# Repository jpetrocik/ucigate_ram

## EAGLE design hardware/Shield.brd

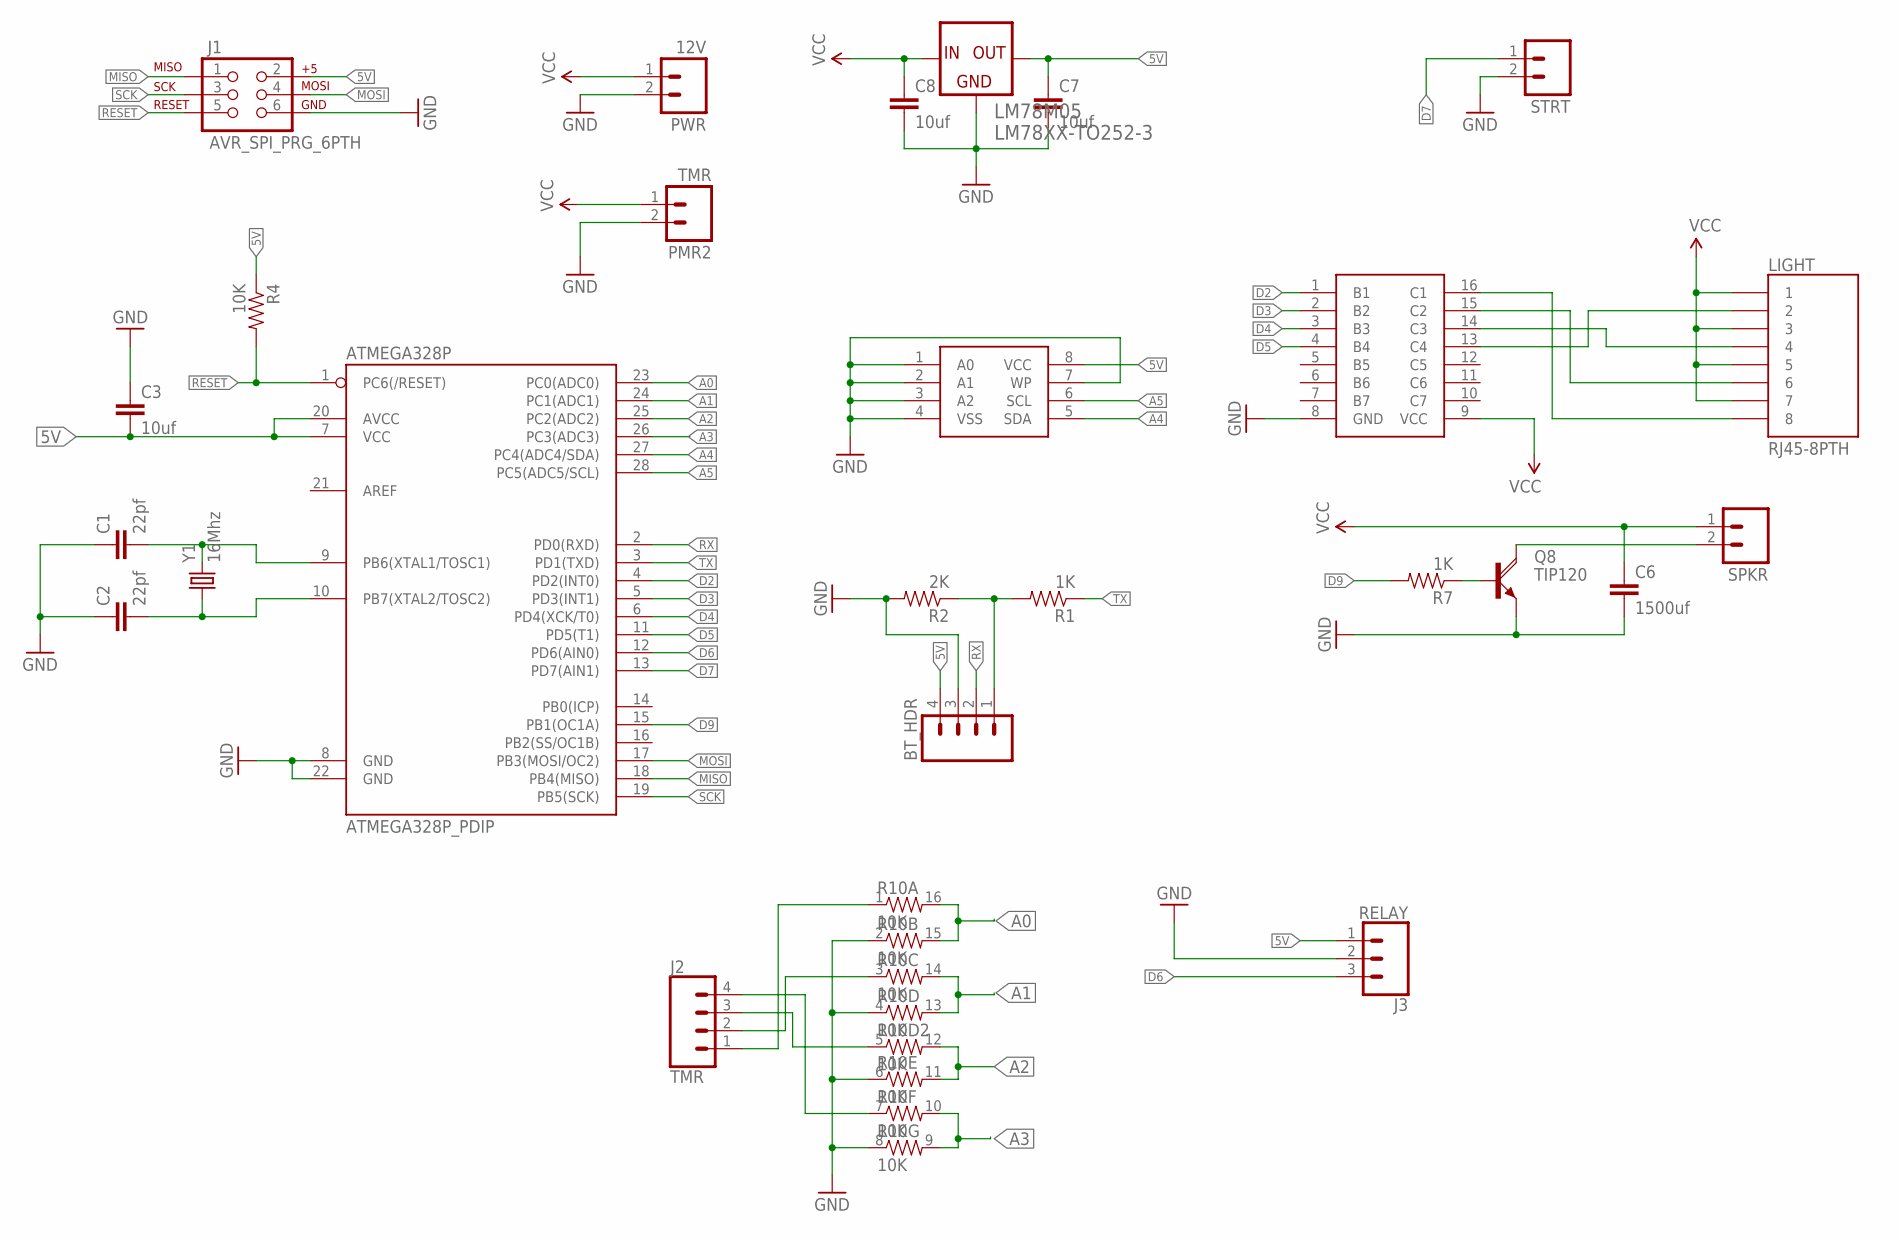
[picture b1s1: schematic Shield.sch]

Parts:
24AA512: 24AAXXX; SOIC-8-EIAJ
ATMEGA328P: ATMEGA328P_PDIP; DIL28-3
BT_HDR: M04PTH; 1X04@1
C1, C2: 22pf; 1206
C3: 10uf; 1206
C6: 1500uf; CAP-PTH-5MM
C7, C8: 10uf; CAP-PTH-SMALL
J1: AVR_SPI_PRG_6PTH; 2X3
J2: TMR; SCREWTERMINAL-3.5MM-4
J3: RELAY; SCREWTERMINAL-3.5MM-3
LIGHT: RJ45-8PTH; RJ45-8
LM78M05: LM78XX-TO252-3; TO252-3
MC1413D: MC1413D; SO016
PMR2: TMR; SCREWTERMINAL-3.5MM-2
PWR: 12V; SCREWTERMINAL-3.5MM-2
Q8: TIP120; TO220V
R1, R7: 1K; 1206
R2: 2K; 1206
R4: 10K; 1206
R10: 10K; SO016
SPKR: M023.5MM; SCREWTERMINAL-3.5MM-2
STRT: M023.5MM; SCREWTERMINAL-3.5MM-2
Y1: 16Mhz; HC49US

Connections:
5V: 24AA512.8 (VCC), ATMEGA328P.7 (VCC), ATMEGA328P.20 (AVCC), BT_HDR.4, C3.2, C7.1, J1.2, J3.1, LM78M05.3 (OUT), R4.1
A0: ATMEGA328P.23 (PC0(ADC0)), R10.15 (2), R10.16 (2)
A1: ATMEGA328P.24 (PC1(ADC1)), R10.13 (2), R10.14 (2)
A2: ATMEGA328P.25 (PC2(ADC2)), R10.11 (2), R10.12 (2)
A3: ATMEGA328P.26 (PC3(ADC3)), R10.9 (2), R10.10 (2)
A4: 24AA512.5 (SDA), ATMEGA328P.27 (PC4(ADC4/SDA))
A5: 24AA512.6 (SCL), ATMEGA328P.28 (PC5(ADC5/SCL))
D2: ATMEGA328P.4 (PD2(INT0)), MC1413D.1 (B1)
D3: ATMEGA328P.5 (PD3(INT1)), MC1413D.2 (B2)
D4: ATMEGA328P.6 (PD4(XCK/T0)), MC1413D.3 (B3)
D5: ATMEGA328P.11 (PD5(T1)), MC1413D.4 (B4)
D6: ATMEGA328P.12 (PD6(AIN0)), J3.3
D7: ATMEGA328P.13 (PD7(AIN1)), STRT.1
D9: ATMEGA328P.15 (PB1(OC1A)), R7.2
GND: 24AA512.1 (A0), 24AA512.2 (A1), 24AA512.3 (A2), 24AA512.4 (VSS), 24AA512.7 (WP), ATMEGA328P.8 (GND), ATMEGA328P.22 (GND), BT_HDR.3, C1.1, C2.1, C3.1, C6.2, C7.2, C8.2, J1.6, J3.2, LM78M05.2 (COM), MC1413D.8 (GND), PMR2.2, PWR.2, Q8.3 (E), R2.2, R10.2 (1), R10.4 (1), R10.6 (1), R10.8 (1), STRT.2
MISO: ATMEGA328P.18 (PB4(MISO)), J1.1
MOSI: ATMEGA328P.17 (PB3(MOSI/OC2)), J1.4
unnamed: BT_HDR.1, R1.2, R2.1
unnamed: LIGHT.8, MC1413D.16 (C1)
unnamed: LIGHT.4, MC1413D.14 (C3)
unnamed: LIGHT.2, MC1413D.13 (C4)
unnamed: LIGHT.6, MC1413D.15 (C2)
unnamed: J2.1, R10.1
unnamed: J2.4, R10.7 (1)
unnamed: Q8.2 (C), SPKR.2
unnamed: ATMEGA328P.9 (PB6(XTAL1/TOSC1)), C1.2, Y1.2
unnamed: J2.2, R10.3 (1)
unnamed: Q8.1 (B), R7.1
unnamed: J2.3, R10.5 (1)
unnamed: ATMEGA328P.10 (PB7(XTAL2/TOSC2)), C2.2, Y1.1
RESET: ATMEGA328P.1 (PC6(/RESET)), J1.5, R4.2
RX: ATMEGA328P.2 (PD0(RXD)), BT_HDR.2
SCK: ATMEGA328P.19 (PB5(SCK)), J1.3
TX: ATMEGA328P.3 (PD1(TXD)), R1.1
VCC: C6.1, C8.1, LIGHT.1, LIGHT.3, LIGHT.5, LIGHT.7, LM78M05.1 (IN), MC1413D.9 (VCC), PMR2.1, PWR.1, SPKR.1

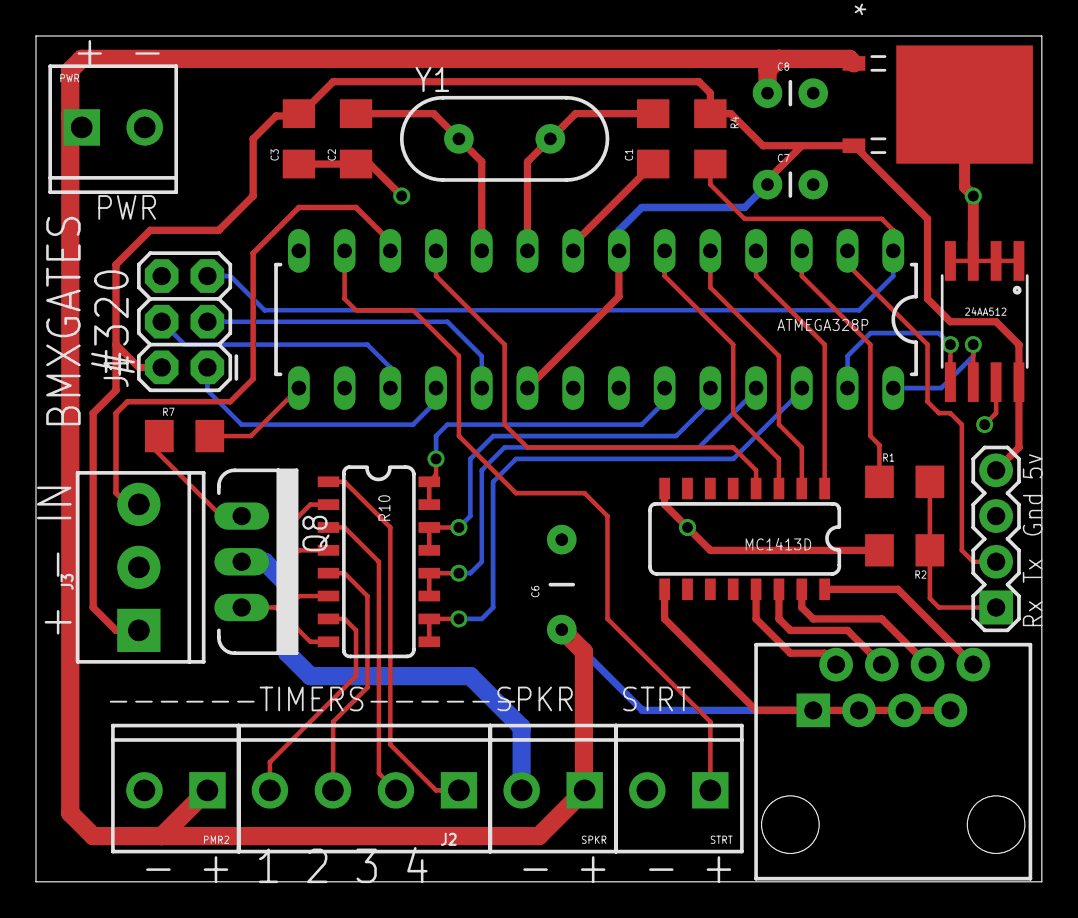
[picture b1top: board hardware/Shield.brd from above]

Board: 2 copper layers, 55.9 x 47.0 mm, 26 parts (0 on the bottom side), 35 nets.

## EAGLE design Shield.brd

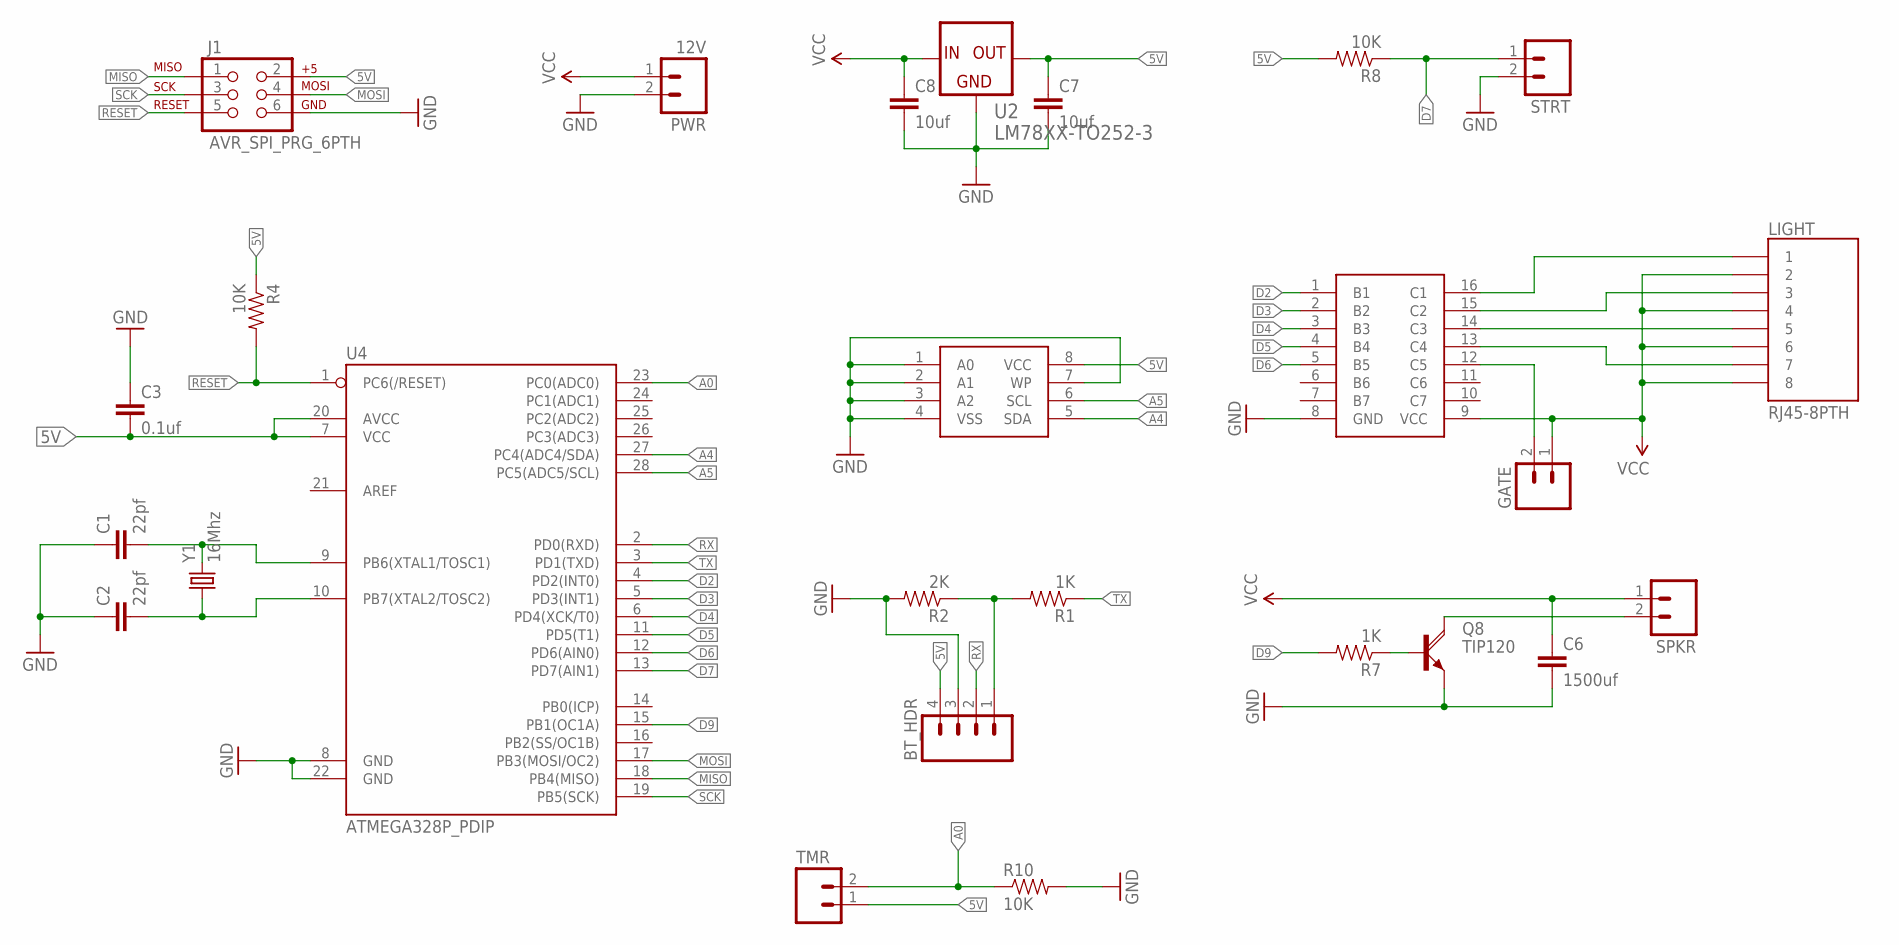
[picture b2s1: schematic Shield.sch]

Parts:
BT_HDR: M04PTH; 1X04
C1, C2: 22pf; 1206
C3: 0.1uf; 1206
C6: 1500uf; CAP-PTH-5MM
C7, C8: 10uf; CAP-PTH-SMALL
GATE: M023.5MM; SCREWTERMINAL-3.5MM-2
J1: AVR_SPI_PRG_6PTH; 2X3
LIGHT: RJ45-8PTH; RJ45-8
PWR: 12V; SCREWTERMINAL-3.5MM-2
Q8: TIP120; TO220V
R1, R7: 1K; 1206
R2: 2K; 1206
R4, R8, R10: 10K; 1206
SPKR: M023.5MM; SCREWTERMINAL-3.5MM-2
STRT: M023.5MM; SCREWTERMINAL-3.5MM-2
TMR: M023.5MM; SCREWTERMINAL-3.5MM-2
U2: LM78XX-TO252-3; TO252-3
U4: ATMEGA328P_PDIP; DIL28-3
U$1: MC1413D; SO016
U$2: 24AAXXX; SOIC-8-EIAJ
Y1: 16Mhz; HC49US

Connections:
5V: BT_HDR.4, C3.2, C7.1, J1.2, R4.1, R8.2, TMR.1, U2.3 (OUT), U4.7 (VCC), U4.20 (AVCC), U$2.8 (VCC)
A0: R10.1, TMR.2, U4.23 (PC0(ADC0))
A4: U4.27 (PC4(ADC4/SDA)), U$2.5 (SDA)
A5: U4.28 (PC5(ADC5/SCL)), U$2.6 (SCL)
D2: U4.4 (PD2(INT0)), U$1.1 (B1)
D3: U4.5 (PD3(INT1)), U$1.2 (B2)
D4: U4.6 (PD4(XCK/T0)), U$1.3 (B3)
D5: U4.11 (PD5(T1)), U$1.4 (B4)
D6: U4.12 (PD6(AIN0)), U$1.5 (B5)
D7: R8.1, STRT.1, U4.13 (PD7(AIN1))
D9: R7.2, U4.15 (PB1(OC1A))
GATE: GATE.2, U$1.12 (C5)
GND: BT_HDR.3, C1.1, C2.1, C3.1, C6.2, C7.2, C8.2, J1.6, PWR.2, Q8.3 (E), R2.2, R10.2, STRT.2, U2.2 (COM), U4.8 (GND), U4.22 (GND), U$1.8 (GND), U$2.1 (A0), U$2.2 (A1), U$2.3 (A2), U$2.4 (VSS), U$2.7 (WP)
MISO: J1.1, U4.18 (PB4(MISO))
MOSI: J1.4, U4.17 (PB3(MOSI/OC2))
unnamed: BT_HDR.1, R1.2, R2.1
unnamed: LIGHT.1, U$1.16 (C1)
unnamed: LIGHT.3, U$1.15 (C2)
unnamed: LIGHT.5, U$1.14 (C3)
unnamed: LIGHT.7, U$1.13 (C4)
unnamed: Q8.2 (C), SPKR.2
unnamed: C1.2, U4.9 (PB6(XTAL1/TOSC1)), Y1.2
unnamed: Q8.1 (B), R7.1
unnamed: C2.2, U4.10 (PB7(XTAL2/TOSC2)), Y1.1
RESET: J1.5, R4.2, U4.1 (PC6(/RESET))
RX: BT_HDR.2, U4.2 (PD0(RXD))
SCK: J1.3, U4.19 (PB5(SCK))
TX: R1.1, U4.3 (PD1(TXD))
VCC: C6.1, C8.1, GATE.1, LIGHT.2, LIGHT.4, LIGHT.6, LIGHT.8, PWR.1, SPKR.1, U2.1 (IN), U$1.9 (VCC)

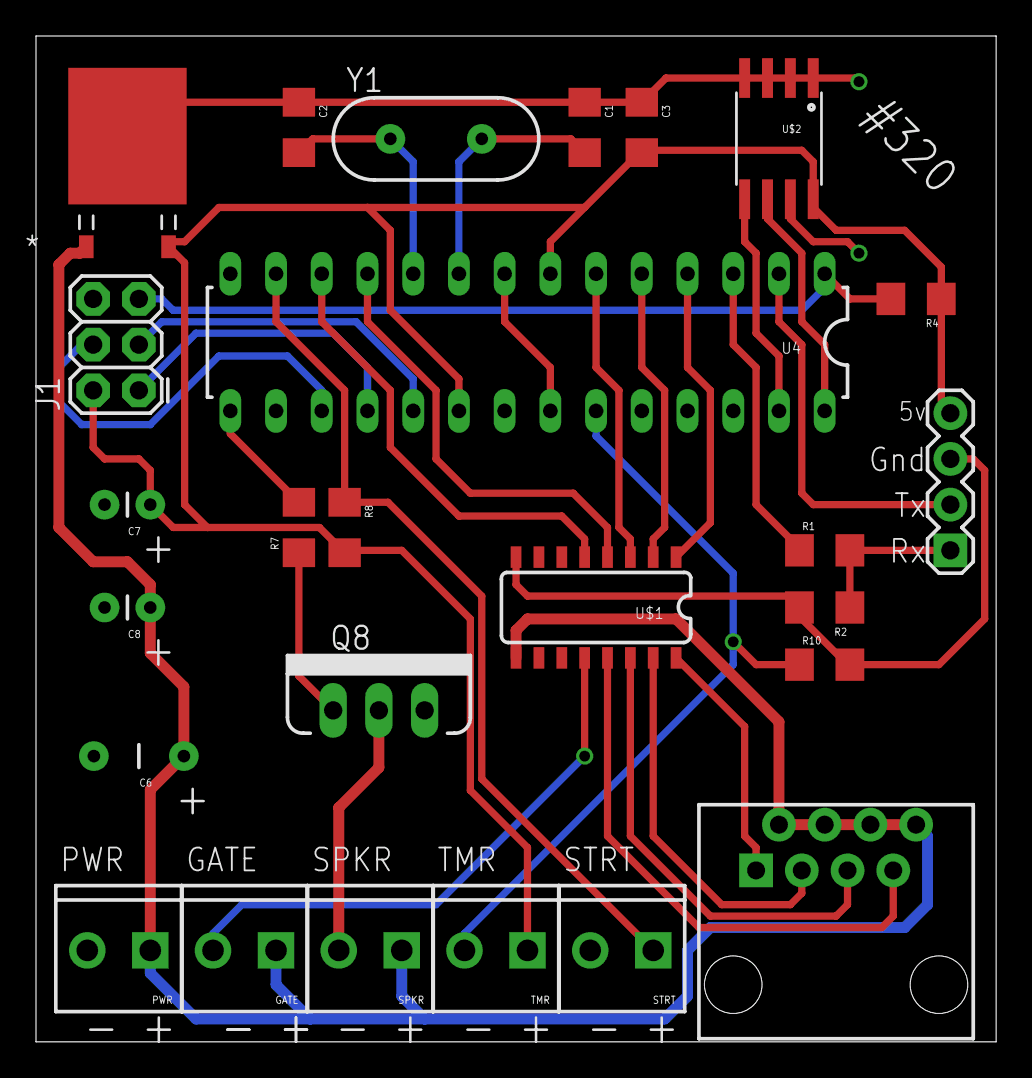
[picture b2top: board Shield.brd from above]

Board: 2 copper layers, 53.3 x 55.9 mm, 26 parts (0 on the bottom side), 29 nets.

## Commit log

2014-10-30 3.X r56
2014-11-07 Converted to single board
2014-11-09 Final 3.0
2014-12-05 Improvement component placement
2014-12-05 Added missing trace
2014-12-05 Update revision number
2017-11-13 Fixed 12v relay voltage
2017-11-13 Moved to hardware
2017-11-13 Merged firmware into hardwre project to keep them together
2017-11-13 Adding README
2017-11-13 Rename to firmware.ino
2017-11-13 Restored lost RAM board design during migration from svn
2017-11-13 Removed MAG_GATE
2017-11-13 Change BOARD DEFINE version to all 3.x boards
2017-11-13 Adding gitignore
2017-11-13 Fixed rogue wires
2017-11-20 Whittier
2017-11-24 Untested timer logic
2018-02-22 Starting 4.3 board developement
2018-02-22 Fix nextSplitTimer assignment
2018-02-22 Fixed reversed pos/neg labels for power
2018-03-11 Moved main cap
2018-03-11 Removed outdate board pin configuration
2018-03-16 Changed light pin configuration
2018-03-16 Fixed positive and negative labels
2018-03-16 Fixed gnd plan shape
2023-08-29 Fix light for whitter bmx

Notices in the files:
parts and their libraries:
SparkFun-Passives: Licensing: CC v3.0 Share-Alike You are welcome to use this library for commercial purposes.
SparkFun-DigitalIC: Licensing: Creative Commons ShareAlike 4.0 International - https://creativecommons.org/licenses/by-sa/4.0
